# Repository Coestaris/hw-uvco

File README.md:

# μVCO - voltage-controlled oscillator for a modular synthesizer

> **AI use.** The authors use AI for additional validation, component research, testbench setup and simulation, intermediate design reviews, release setup, and assistance with KiCad and 3D model edits. The authors developed the original designs and schematics manually, and other people reviewed them. The authors make the technical and visual decisions and take responsibility for them.

uvco is a voltage-controlled oscillator for a modular synthesizer.
Rev1 has a published manufacturing release. Rev2 is a work in progress.

## Hardware projects

| Board | Purpose | Design | Simulation |
| --- | --- | --- | --- |
| Rev1 | Saw and pulse oscillator with PWM | [KiCad project](hardware/rev1/uvco_rev1.kicad_pro) | |
| Rev2 | Analog oscillator with saw, triangle, and sine shaping | [KiCad project](hardware/rev2/uvco_rev2.kicad_pro) | [ngspice bench](sim/rev2/) |

## rev1

Rev1 combines exponential pitch control with a CD40106B oscillator core and a buffered mix of saw and pulse waves. The front panel provides coarse and fine tuning, V/oct and attenuated FM inputs, and manual duty and PWM controls.

Rev1 accepts ±12 V through a 10-pin header. The 78L08 and 79L08 regulators supply the ±8 V analog rails. TL074 amplifiers handle control summing, signal conditioning, mixing, and indication. BC847C and BC857C transistors form part of the discrete control circuit. Test points and indicators support bring-up and calibration.

```mermaid
flowchart LR
    Pitch["V/oct · FM · coarse/fine"] --> Control["Pitch summing and exponential converter"]
    Control --> Core["Oscillator core"]
    Core --> Saw["Saw buffer"]
    Saw --> Pulse["Pulse comparator"]
    PWM["Duty control · PWM CV"] --> Pulse
    Saw --> Mix["Saw/pulse mix and output buffer"]
    Pulse --> Mix
    Mix --> Output["OUT"]
    CV["Protected CV inputs"] --> LEDs["Input indicators"]
    Power["±12 V power"] --> Rails["Protection, filtering and ±8 V regulation"]
```

[Rev1 release](https://github.com/Coestaris/hw-uvco/releases/tag/rev1)

<details>
<summary>Top and bottom views</summary>

</details>

| File | Download |
| --- | --- |
| Schematic PDF | [uvco_rev1-schematic.pdf](https://github.com/Coestaris/hw-uvco/releases/download/rev1/uvco_rev1-schematic.pdf) |
| PCB PDF | [uvco_rev1-pcb.pdf](https://github.com/Coestaris/hw-uvco/releases/download/rev1/uvco_rev1-pcb.pdf) |
| Gerbers and drill files | [uvco_rev1-gerbers.zip](https://github.com/Coestaris/hw-uvco/releases/download/rev1/uvco_rev1-gerbers.zip) |
| JLCPCB BOM | [uvco_rev1-jlcpcb-bom.csv](https://github.com/Coestaris/hw-uvco/releases/download/rev1/uvco_rev1-jlcpcb-bom.csv) |
| JLCPCB placement | [uvco_rev1-jlcpcb-pnp.csv](https://github.com/Coestaris/hw-uvco/releases/download/rev1/uvco_rev1-jlcpcb-pnp.csv) |
| 3D assembly model | [uvco_rev1.stpz](https://github.com/Coestaris/hw-uvco/releases/download/rev1/uvco_rev1.stpz) |

#### Hardware bring-up

At first power-up, the oscillator core produced high-frequency, low-amplitude noise, with almost no signal at the output. The prototype needed three fixes.

1. **Pitch control feedback.** The original RV1 configuration prevented normal oscillation. Replacing RV1 with a 10 kΩ resistor in series with R5 in U7C’s feedback loop restored oscillation.

   <details>
   <summary>RV1 feedback schematic</summary>

   </details>

2. **Signal LEDs.** A 2 kΩ pull-down from the cathode of D10 to ground gave C23 a discharge path through RV9 when the signal was absent, restoring LED indication.

   <details>
   <summary>LED discharge schematic</summary>

   </details>

3. **Duty-cycle control.** A PCB etching defect affected the `pwm_protected` trace between R28 pad 2 and U7 pin 7. Repairing the connection restored duty-cycle control.

   <details>
   <summary>PWM trace on the PCB</summary>

   </details>

#### Bench test results

- **Frequency range.** The repaired board produced usable waveforms from about 60 Hz up to 6–7 kHz. Above that range, the frequency jumped sharply and the oscillator saturated.
- **Pulse duty cycle.** The control adjusted the pulse width smoothly and predictably over nearly the full 0–100% range.
- **Output offset.** Changing the frequency produced a small baseline shift at the AC-coupled output.
- **Pitch tracking.** Tuning was coarse and temperature-dependent, limiting its accuracy for musical intervals.

## rev2

The Rev2 oscillator uses a matched DMMT3904 transistor pair for exponential current control. An integrator generates a sawtooth ramp, and a comparator triggers the reset. A triangle shaper feeds the LM13700 sine shaper. The design accepts ±12 V and derives local reference rails.

The ngspice bench includes frequency, sensitivity, and stability sweeps. The full oscillator-to-sine simulation sustained oscillation at all 37 control-voltage points tested.

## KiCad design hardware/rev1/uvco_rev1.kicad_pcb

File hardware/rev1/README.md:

# VCO1 Rev1

KiCad sources are in this directory; JLCPCB production files are in `manufacturing/`.
The same directory contains a four-page schematic PDF and a seven-page PCB PDF:
front silkscreen with pad apertures, mirrored back silkscreen with pad
apertures, front copper, mirrored back copper, top 3D, bottom 3D, and a
perspective corner view. Technical PCB pages are cropped to the `Edge.Cuts`
bounds. They exclude the fabrication/manufacturing-data layers and drawing-sheet
table/frame. KiCad text remains searchable in the PDFs.

Regenerate both PDFs without the KiCad GUI:

```sh
uv run --project tools release export vco1_rev1
```

Gerber, BOM, and pick-and-place generation is available through explicit flags
and is disabled by default. See the repository-level `README.md` for the shared
generator and software requirements.

The assembly BOM was audited against the JLCPCB catalog on 2026-07-14. It has
16 Basic line items, 6 Promotional Extended line items that JLC currently
exempts from feeder-loading fees for Economic assembly, and 3 fee-bearing
Extended line items. The remaining fee-bearing parts are the 10k B3950 NTC and
the positive/negative 8V regulators; no electrically safe Basic or Promotional
replacement was available. R29 changed from 14k to the Basic 15k value, a 7.1%
change that only affects PWM control scaling. Recheck Promotional status and
stock when uploading the BOM because JLCPCB catalog classifications can change.

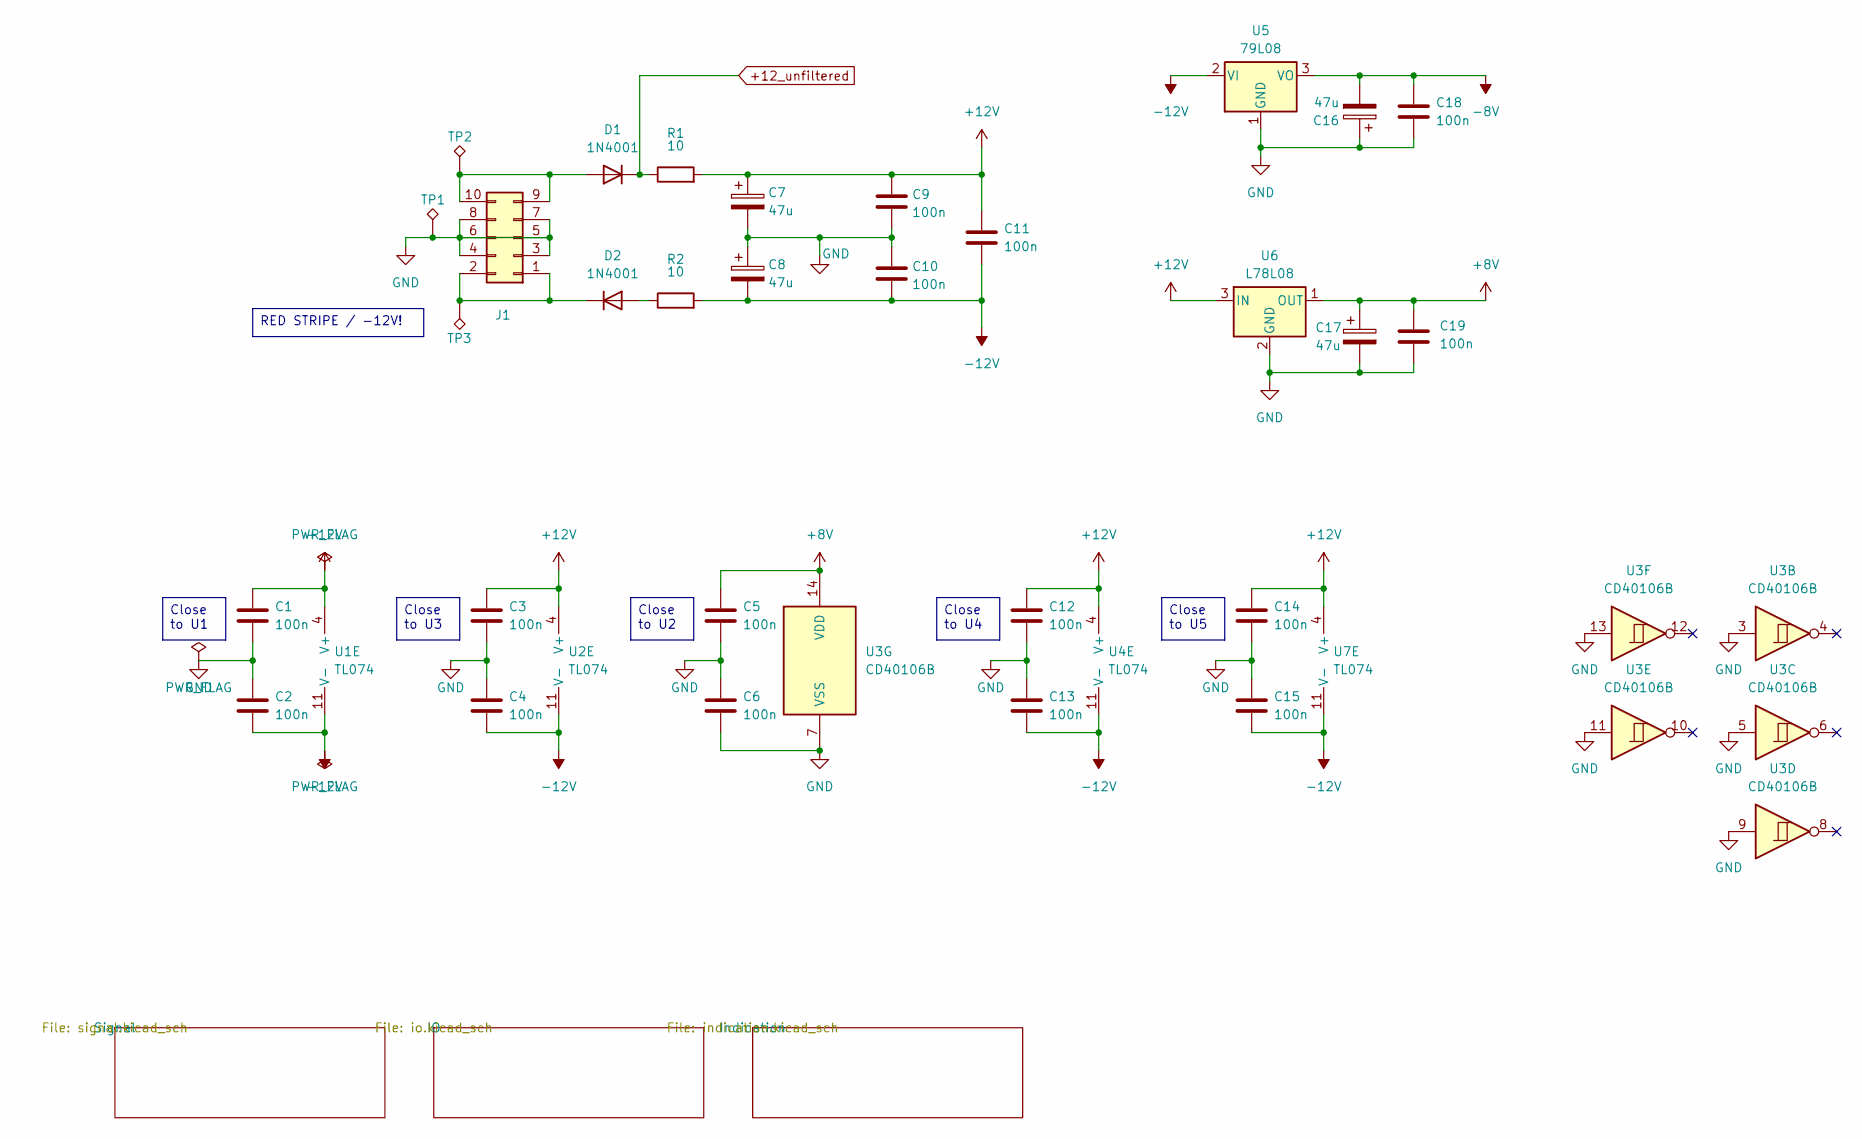
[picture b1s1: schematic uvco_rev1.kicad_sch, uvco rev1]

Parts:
C1, C2, C3, C4, C5, C6, C9, C10, C11, C12, C13, C14, C15, C18, C19: 100n; C_0805_2012Metric; LCSC Part # C49678
C7, C8, C16, C17: 47u; CP_Radial_D10.0mm_P3.80mm
D1, D2: 1N4001; D_SOD-123F; LCSC Part # C18199085
J1: Conn_02x05_Odd_Even; IDC-Header_2x05_P2.54mm_Vertical
R1, R2: 10; R_0805_2012Metric_Pad1.20x1.40mm_HandSolder; LCSC Part # C17415
TP1, TP2, TP3: TestPoint_Alt; TestPoint_Loop_D2.54mm_Drill1.5mm_Beaded
U1, U2, U4, U7: TL074; DIP-14_W10.16mm
U3: CD40106B; DIP-14_W10.16mm
U5: 79L08; SOT-89-3; Manufacturer Part Number 79L08; LCSC Part # C5246138
U6: L78L08; SOT-89-3; LCSC Part # C347270

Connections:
+8V: C5.1, C17.1, C19.1, U3.14 (VDD), U6.1 (OUT); also elsewhere on the board
+12V: C1.1, C3.1, C7.1, C9.1, C11.1, C12.1, C14.1, R1.2, U1.4 (V+), U2.4 (V+), U4.4 (V+), U6.3 (IN), U7.4 (V+); also elsewhere on the board
+12_unfiltered: D1.1 (K), R1.1; also elsewhere on the board
-8V: C16.2, C18.1, U5.3 (VO); also elsewhere on the board
-12V: C2.2, C4.2, C8.2, C10.2, C11.2, C13.2, C15.2, R2.2, U1.11 (V-), U2.11 (V-), U4.11 (V-), U5.2 (VI), U7.11 (V-); also elsewhere on the board
GND: C1.2, C2.1, C3.2, C4.1, C5.2, C6.1, C6.2, C7.2, C8.1, C9.2, C10.1, C12.2, C13.1, C14.2, C15.1, C16.1, C17.2, C18.2, C19.2, J1.3, J1.4, J1.5, J1.6, J1.7, J1.8, TP1.1 (1_1), U3.3, U3.5, U3.7 (VSS), U3.9, U3.11, U3.13, U5.1 (GND), U6.2 (GND); also elsewhere on the board
unnamed: D1.2 (A), J1.9, J1.10, TP2.1 (1_1)
unnamed: D2.2 (A), R2.1
unnamed: D2.1 (K), J1.1, J1.2, TP3.1 (1_1)

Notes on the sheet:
Close to U3
Close to U4
RED STRIPE / -12V!
Close to U1
Close to U2
Close to U5

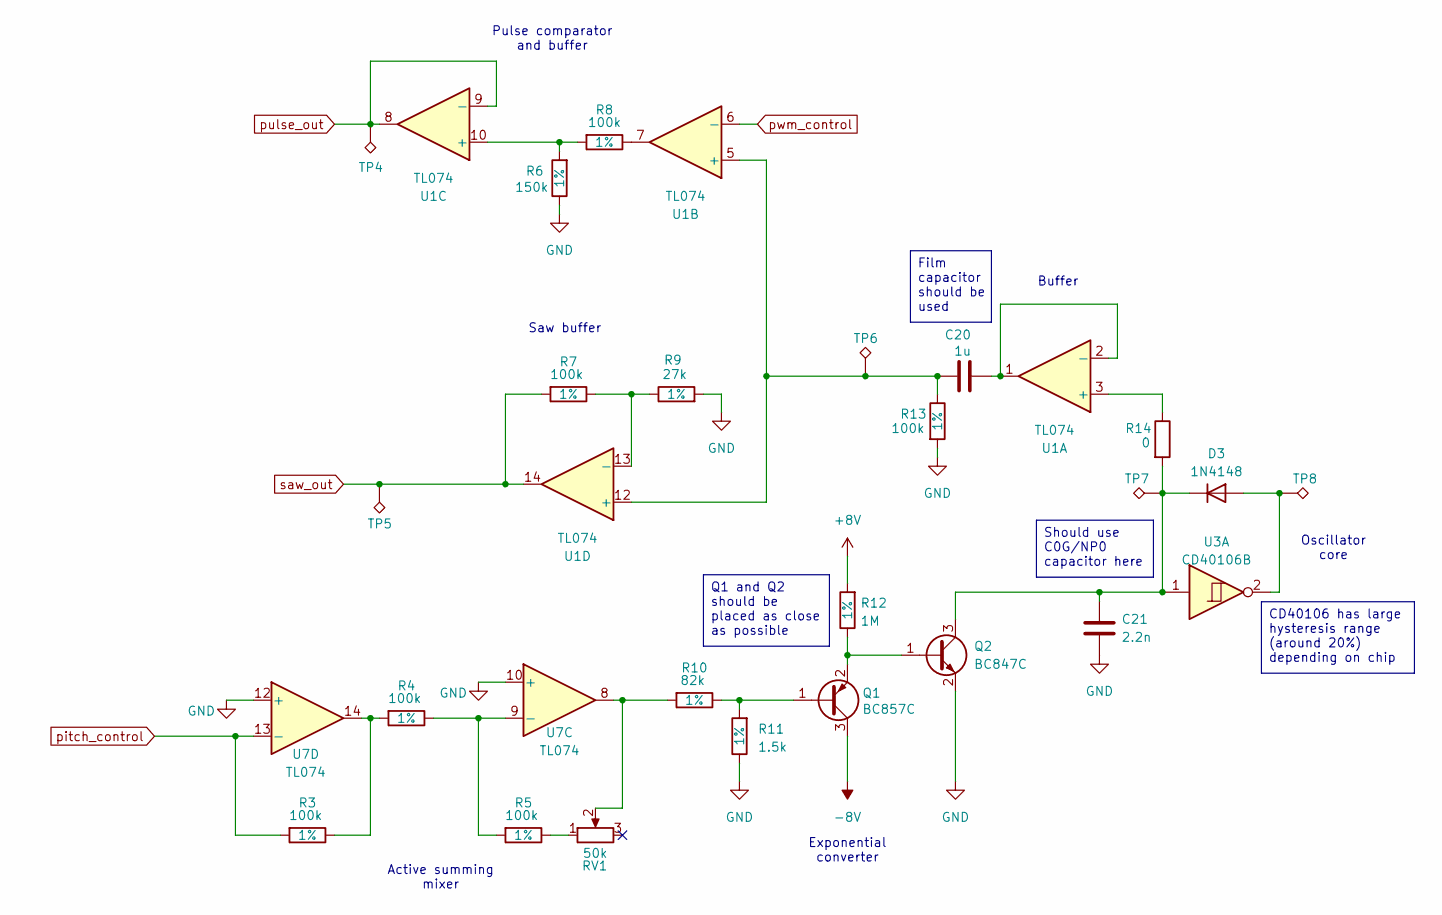
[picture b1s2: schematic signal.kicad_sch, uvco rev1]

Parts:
C20: 1u; C_Axial_L3.8mm_D2.6mm_P7.50mm_Horizontal
C21: 2.2n; C_0805_2012Metric; LCSC Part # C28260
D3: 1N4148; D_SOD-323; LCSC Part # C2128
Q1: BC857C; SOT-23; LCSC Part # C20069137
Q2: BC847C; SOT-23; LCSC Part # C7420337
R3, R4, R5, R7, R8, R13: 100k; R_0805_2012Metric_Pad1.20x1.40mm_HandSolder; Tolerance 1%; LCSC Part # C149504
R6: 150k; R_0805_2012Metric_Pad1.20x1.40mm_HandSolder; Tolerance 1%; LCSC Part # C17470
R9: 27k; R_0805_2012Metric_Pad1.20x1.40mm_HandSolder; Tolerance 1%; LCSC Part # C17593
R10: 82k; R_0805_2012Metric_Pad1.20x1.40mm_HandSolder; Tolerance 1%; LCSC Part # C17840
R11: 1.5k; R_0805_2012Metric_Pad1.20x1.40mm_HandSolder; Tolerance 1%; LCSC Part # C4310
R12: 1M; R_0805_2012Metric_Pad1.20x1.40mm_HandSolder; Tolerance 1%; LCSC Part # C17514
R14: 0; R_0805_2012Metric_Pad1.20x1.40mm_HandSolder; LCSC Part # C17477
RV1: 50k; Potentiometer_Bourns_3296W_Vertical
TP4, TP5, TP6, TP7, TP8: TestPoint_Alt; TestPoint_Loop_D2.54mm_Drill1.5mm_Beaded
U1, U7: TL074; DIP-14_W10.16mm
U3: CD40106B; DIP-14_W10.16mm

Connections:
+8V: R12.2; also elsewhere on the board
-8V: Q1.3 (C); also elsewhere on the board
GND: C21.2, Q2.2 (E), R6.1, R9.2, R11.1, R13.2, U7.10 (+), U7.12 (+); also elsewhere on the board
unnamed: D3.2 (A), TP8.1 (1_1), U3.2
unnamed: C21.1, D3.1 (K), Q2.3 (C), R14.2, TP7.1 (1_1), U3.1
unnamed: Q1.1 (B), R10.1, R11.2
unnamed: Q1.2 (E), Q2.1 (B), R12.1
unnamed: R3.1, R4.2, U7.14
unnamed: R5.1, RV1.1
unnamed: R8.1, U1.7
unnamed: R10.2, RV1.2, U7.8
unnamed: R14.1, U1.3 (+)
unnamed: C20.1, U1.1, U1.2 (-)
unnamed: C20.2, R13.1, TP6.1 (1_1), U1.5 (+), U1.12 (+)
unnamed: R6.2, R8.2, U1.10 (+)
unnamed: R7.1, R9.1, U1.13 (-)
unnamed: R4.1, R5.2, U7.9 (-)
pitch_control: R3.2, U7.13 (-); also elsewhere on the board
pulse_out: TP4.1 (1_1), U1.8, U1.9 (-); also elsewhere on the board
pwm_control: U1.6 (-); also elsewhere on the board
saw_out: R7.2, TP5.1 (1_1), U1.14; also elsewhere on the board

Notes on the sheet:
Active summing mixer
Buffer
Pulse comparator and buffer
Exponential converter
Saw buffer
Oscillator core
Q1 and Q2 should be placed as close as possible
Film capacitor should be used
CD40106 has large hysteresis range (around 20%) depending on chip
Should use C0G/NP0 capacitor here

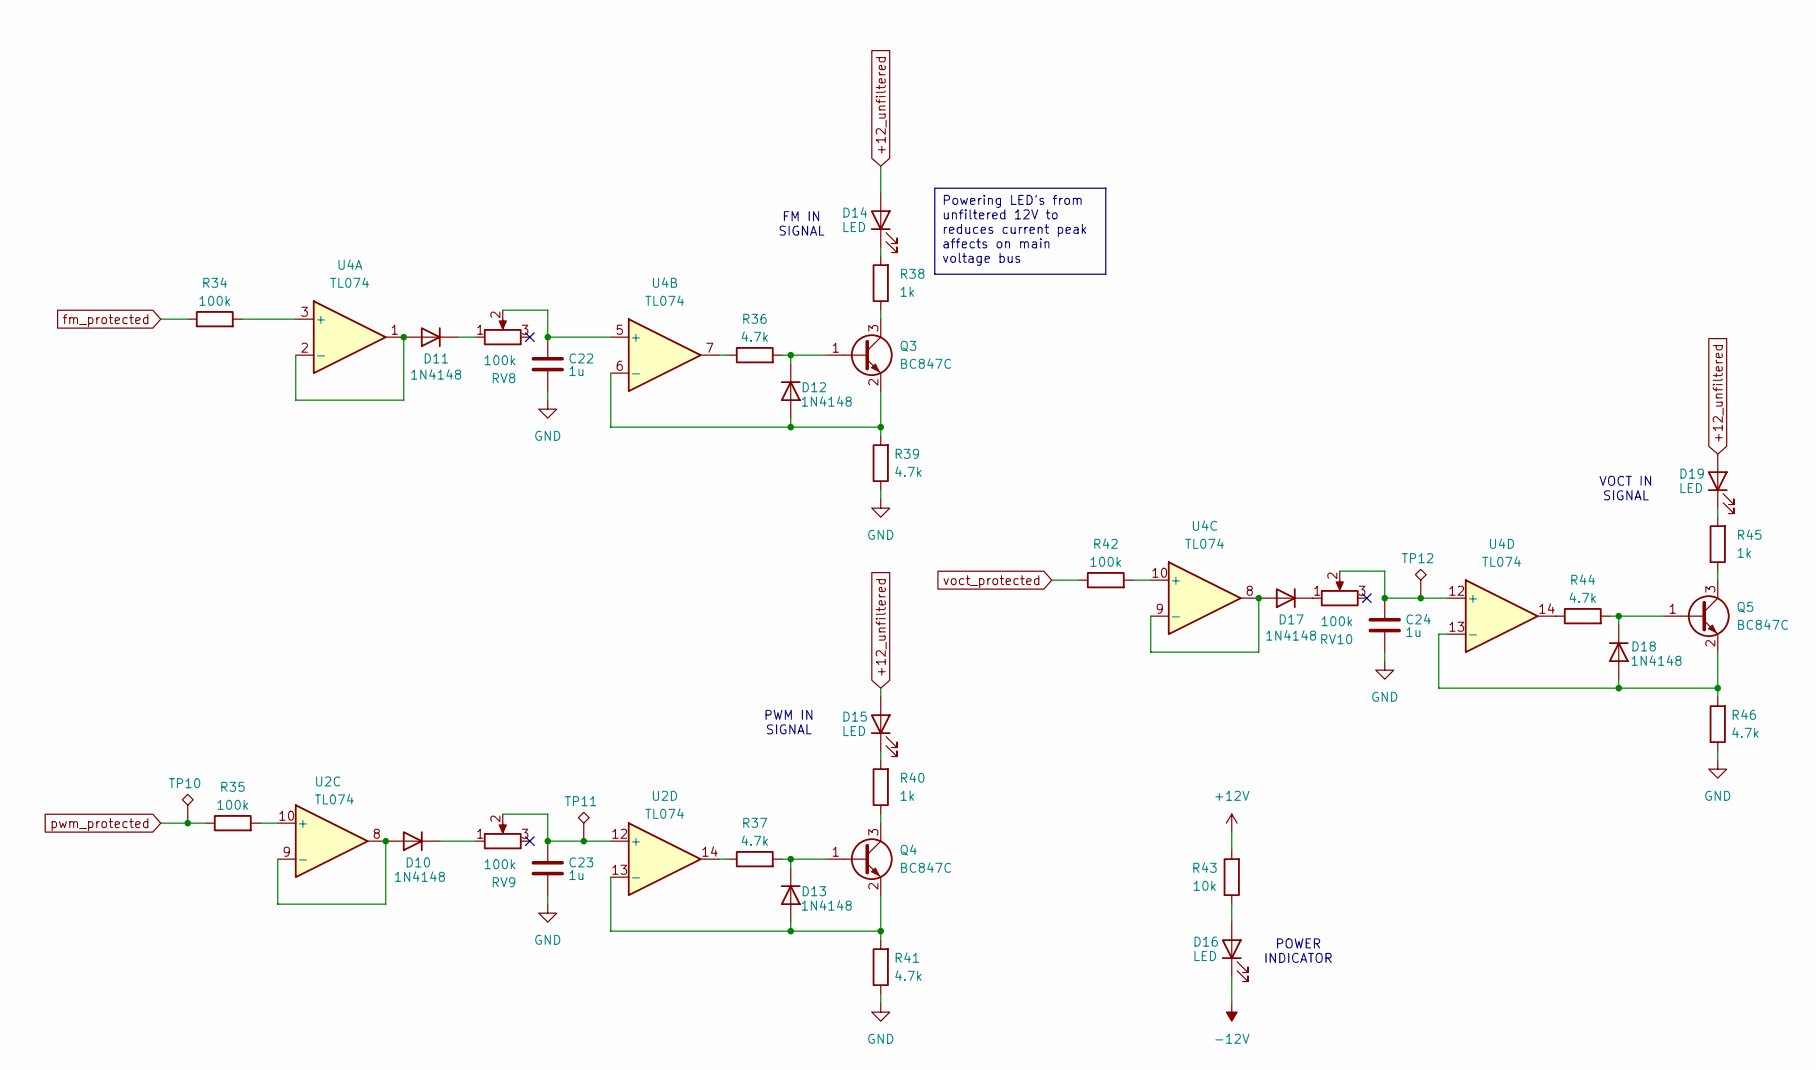
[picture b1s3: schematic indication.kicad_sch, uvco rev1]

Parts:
C22, C23, C24: 1u; C_0805_2012Metric; LCSC Part # C28323
D10, D11, D12, D13, D17, D18: 1N4148; D_SOD-323; LCSC Part # C2128
D14, D15, D16, D19: LED; LED_D3.0mm
Q3, Q4, Q5: BC847C; SOT-23; LCSC Part # C7420337
R34, R35, R42: 100k; R_0805_2012Metric_Pad1.20x1.40mm_HandSolder; LCSC Part # C149504
R36, R37, R39, R41, R44, R46: 4.7k; R_0805_2012Metric_Pad1.20x1.40mm_HandSolder; LCSC Part # C17673
R38, R40, R45: 1k; R_0805_2012Metric_Pad1.20x1.40mm_HandSolder; LCSC Part # C17513
R43: 10k; R_0805_2012Metric_Pad1.20x1.40mm_HandSolder; LCSC Part # C17414
RV8, RV9, RV10: 100k; Potentiometer_Bourns_3296W_Vertical
TP10, TP11, TP12: TestPoint_Alt; TestPoint_Loop_D2.54mm_Drill1.5mm_Beaded
U2, U4: TL074; DIP-14_W10.16mm

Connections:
+12V: R43.2; also elsewhere on the board
+12_unfiltered: D14.2 (A), D15.2 (A), D19.2 (A); also elsewhere on the board
-12V: D16.1 (K); also elsewhere on the board
GND: C22.2, C23.2, C24.2, R39.1, R41.1, R46.1; also elsewhere on the board
unnamed: D10.2 (A), U2.8, U2.9 (-)
unnamed: D10.1 (K), RV9.1
unnamed: D11.2 (A), U4.1, U4.2 (-)
unnamed: D11.1 (K), RV8.1
unnamed: D12.2 (A), Q3.2 (E), R39.2, U4.6 (-)
unnamed: D12.1 (K), Q3.1 (B), R36.2
unnamed: D13.2 (A), Q4.2 (E), R41.2, U2.13 (-)
unnamed: D13.1 (K), Q4.1 (B), R37.2
unnamed: D14.1 (K), R38.2
unnamed: D15.1 (K), R40.2
unnamed: D16.2 (A), R43.1
unnamed: D17.2 (A), U4.8, U4.9 (-)
unnamed: D17.1 (K), RV10.1
unnamed: D18.2 (A), Q5.2 (E), R46.2, U4.13 (-)
unnamed: D18.1 (K), Q5.1 (B), R44.2
unnamed: D19.1 (K), R45.2
unnamed: Q3.3 (C), R38.1
unnamed: Q4.3 (C), R40.1
unnamed: Q5.3 (C), R45.1
unnamed: R36.1, U4.7
unnamed: R37.1, U2.14
unnamed: R44.1, U4.14
unnamed: R35.2, U2.10 (+)
unnamed: C23.1, RV9.2, TP11.1 (1_1), U2.12 (+)
unnamed: R34.2, U4.3 (+)
unnamed: C22.1, RV8.2, U4.5 (+)
unnamed: R42.2, U4.10 (+)
unnamed: C24.1, RV10.2, TP12.1 (1_1), U4.12 (+)
fm_protected: R34.1; also elsewhere on the board
pwm_protected: R35.1, TP10.1 (1_1); also elsewhere on the board
voct_protected: R42.1; also elsewhere on the board

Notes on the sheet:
POWER INDICATOR
FM IN SIGNAL
PWM IN SIGNAL
VOCT IN SIGNAL
Powering LED's from unfiltered 12V to reduces current peak affects on main voltage bus

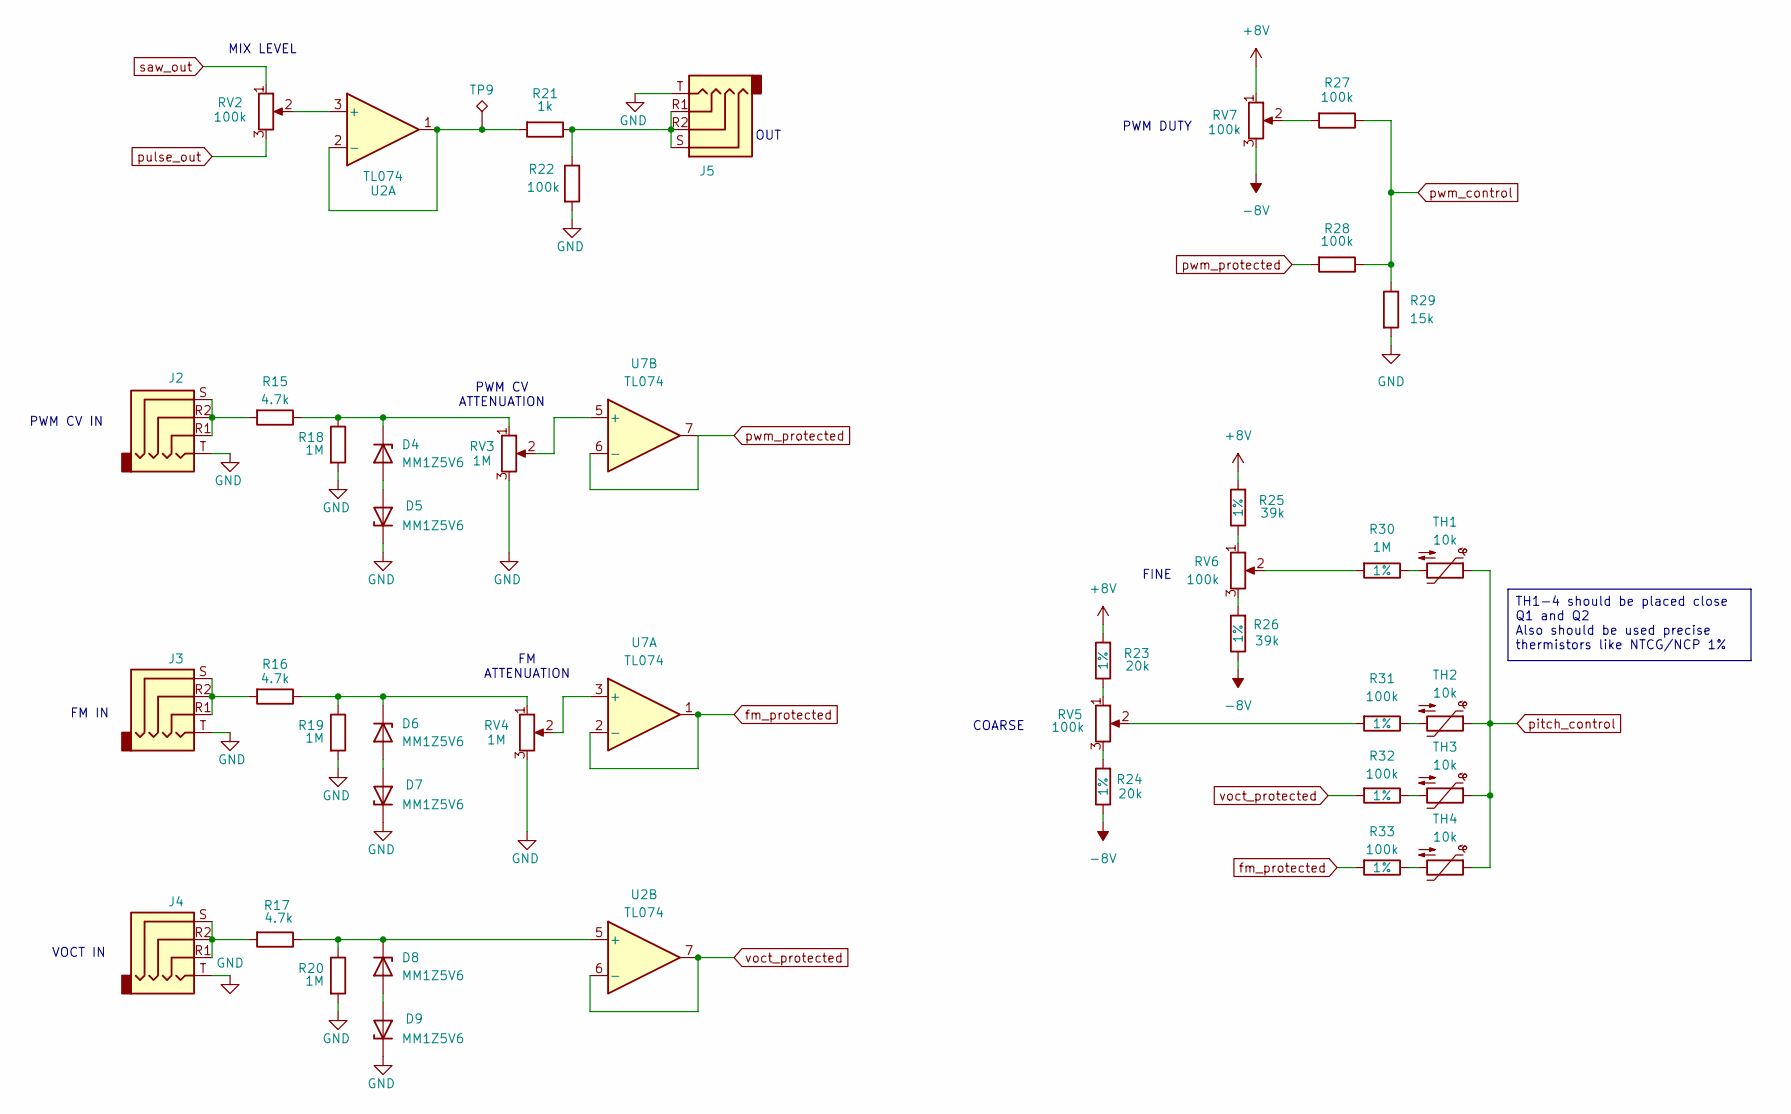
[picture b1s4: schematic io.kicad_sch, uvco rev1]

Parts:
D4, D5, D6, D7, D8, D9: MM1Z5V6; D_SOD-123; LCSC Part # C22395539
J2, J3, J4, J5: AudioJack2; Jack_3.5mm_PJ320E_Horizontal
R15, R16, R17: 4.7k; R_0805_2012Metric_Pad1.20x1.40mm_HandSolder; LCSC Part # C17673
R18, R19, R20: 1M; R_0805_2012Metric_Pad1.20x1.40mm_HandSolder; LCSC Part # C17514
R21: 1k; R_0805_2012Metric_Pad1.20x1.40mm_HandSolder; LCSC Part # C17513
R22, R27, R28: 100k; R_0805_2012Metric_Pad1.20x1.40mm_HandSolder; LCSC Part # C149504
R23, R24: 20k; R_0805_2012Metric_Pad1.20x1.40mm_HandSolder; Tolerance 1%; LCSC Part # C4328
R25, R26: 39k; R_0805_2012Metric_Pad1.20x1.40mm_HandSolder; Tolerance 1%; LCSC Part # C25826
R29: 15k; R_0805_2012Metric_Pad1.20x1.40mm_HandSolder; LCSC Part # C17475
R30: 1M; R_0805_2012Metric_Pad1.20x1.40mm_HandSolder; Tolerance 1%; LCSC Part # C17514
R31, R32, R33: 100k; R_0805_2012Metric_Pad1.20x1.40mm_HandSolder; Tolerance 1%; LCSC Part # C149504
RV2, RV5, RV6, RV7: 100k; Potentiometer_Alps_RK163_Single_Horizontal
RV3, RV4: 1M; Potentiometer_Alps_RK163_Single_Horizontal
TH1, TH2, TH3, TH4: 10k; R_0402_1005Metric; LCSC Part # C49247682
TP9: TestPoint_Alt; TestPoint_Loop_D2.54mm_Drill1.5mm_Beaded
U2, U7: TL074; DIP-14_W10.16mm

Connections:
+8V: R23.2, R25.2, RV7.1; also elsewhere on the board
-8V: R24.1, R26.1, RV7.3; also elsewhere on the board
GND: D5.1 (K), D7.1 (K), D9.1 (K), J2.T, J3.T, J4.T, J5.T, R18.2, R19.2, R20.2, R22.2, R29.2, RV3.3, RV4.3; also elsewhere on the board
unnamed: D4.2 (A), D5.2 (A)
unnamed: D4.1 (K), R15.1, R18.1, RV3.1
unnamed: D6.2 (A), D7.2 (A)
unnamed: D6.1 (K), R16.1, R19.1, RV4.1
unnamed: D8.2 (A), D9.2 (A)
unnamed: D8.1 (K), R17.1, R20.1, U2.5 (+)
unnamed: J2.R1, J2.R2, J2.S, R15.2
unnamed: J3.R1, J3.R2, J3.S, R16.2
unnamed: J4.R1, J4.R2, J4.S, R17.2
unnamed: J5.R1, J5.R2, J5.S, R21.1, R22.1
unnamed: R23.1, RV5.1
unnamed: R24.2, RV5.3
unnamed: R25.1, RV6.1
unnamed: R26.2, RV6.3
unnamed: R27.2, RV7.2
unnamed: R30.1, TH1.2
unnamed: R30.2, RV6.2
unnamed: R31.1, TH2.2
unnamed: R31.2, RV5.2
unnamed: R32.1, TH3.2
unnamed: R33.1, TH4.2
unnamed: RV2.2, U2.3 (+)
unnamed: R21.2, TP9.1 (1_1), U2.1, U2.2 (-)
unnamed: RV4.2, U7.3 (+)
unnamed: RV3.2, U7.5 (+)
fm_protected: R33.2, U7.1, U7.2 (-); also elsewhere on the board
pitch_control: TH1.1, TH2.1, TH3.1, TH4.1; also elsewhere on the board
pulse_out: RV2.3; also elsewhere on the board
pwm_control: R27.1, R28.1, R29.1; also elsewhere on the board
pwm_protected: R28.2, U7.6 (-), U7.7; also elsewhere on the board
saw_out: RV2.1; also elsewhere on the board
voct_protected: R32.2, U2.6 (-), U2.7; also elsewhere on the board

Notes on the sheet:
MIX LEVEL
COARSE
PWM DUTY
PWM CV ATTENUATION
OUT
VOCT IN
PWM CV IN
FM ATTENUATION
FINE
FM IN
TH1-4 should be placed close Q1 and Q2 Also should be used precise thermistors like NTCG/NCP 1%

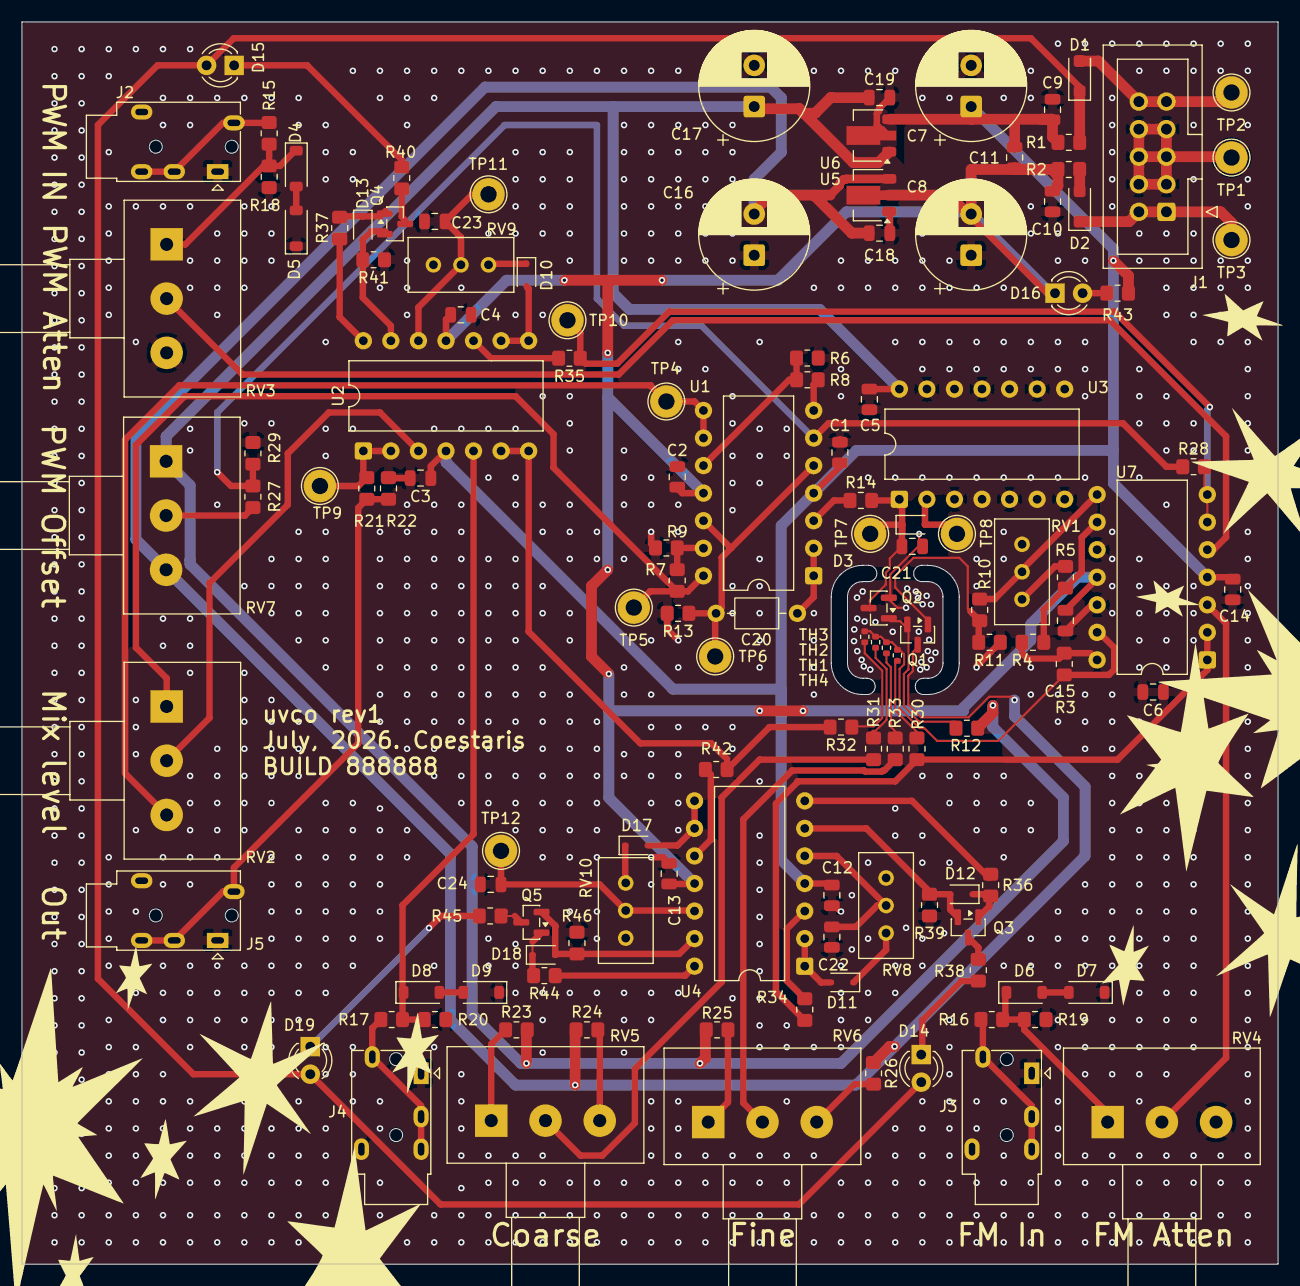
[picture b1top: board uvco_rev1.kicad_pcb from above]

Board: 2 copper layers, 115.8 x 114.5 mm, 132 parts (0 on the bottom side), 83 nets.
